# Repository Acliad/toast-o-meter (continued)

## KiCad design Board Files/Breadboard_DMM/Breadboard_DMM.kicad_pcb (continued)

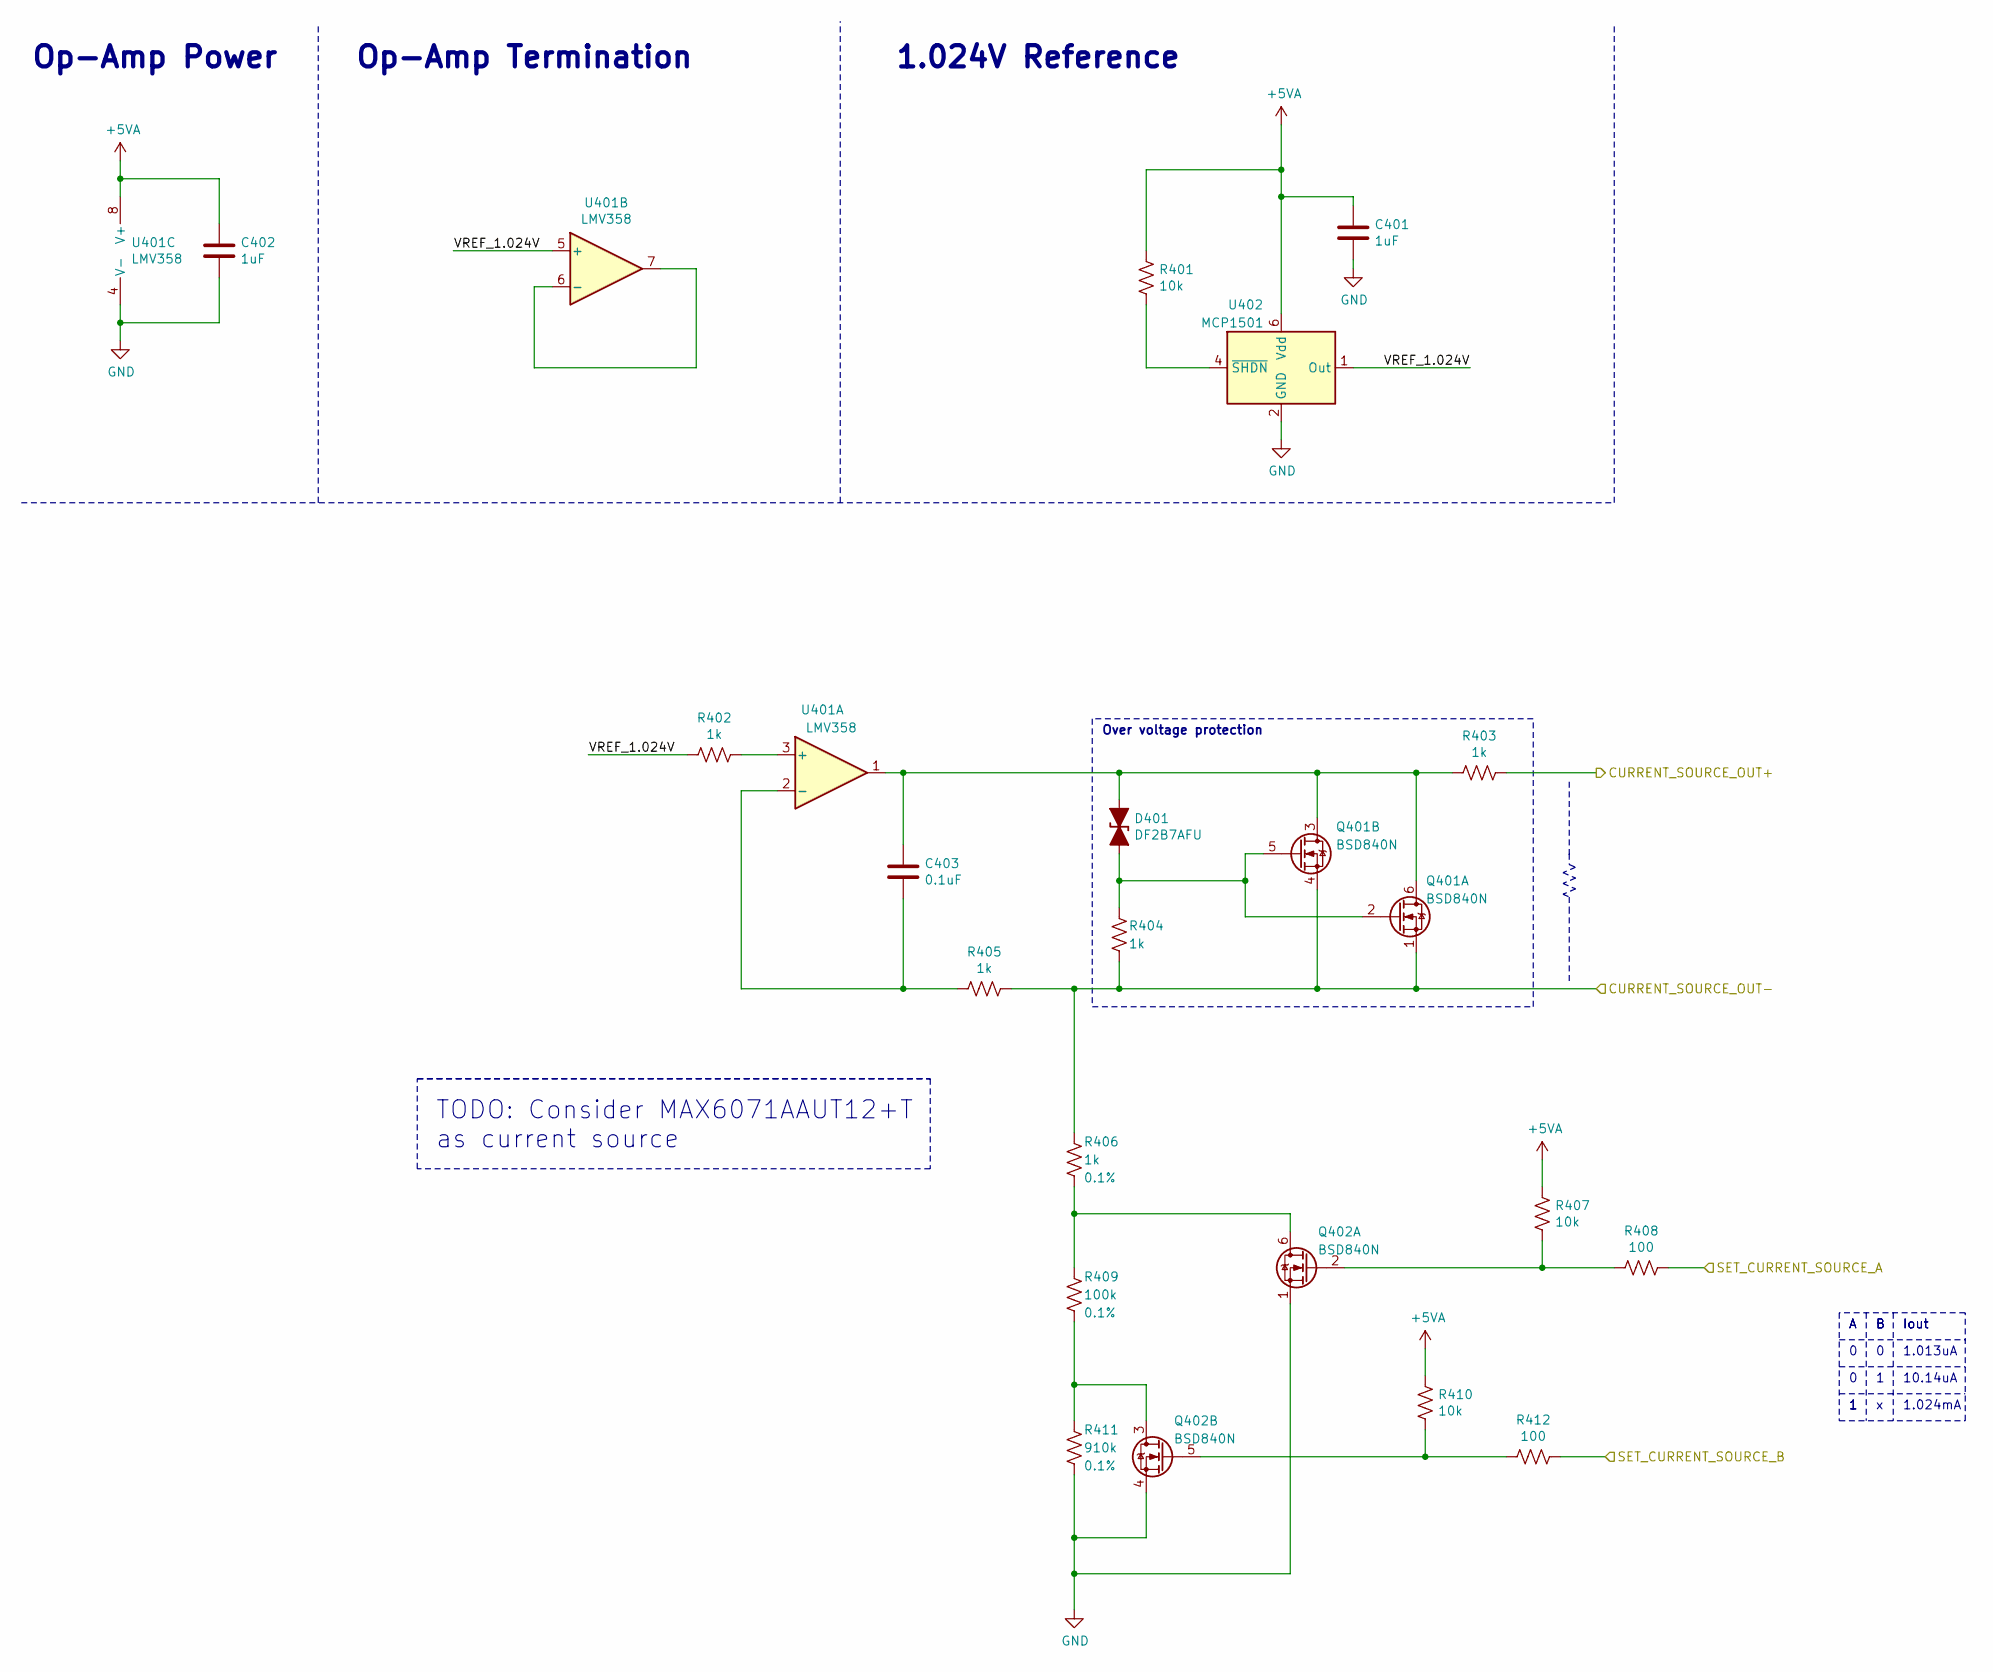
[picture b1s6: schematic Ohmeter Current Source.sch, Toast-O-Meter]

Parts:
C401, C402: 1uF; C_0603_1608Metric_Pad1.08x0.95mm_HandSolder; Digi-Key PN 1276-6524-1-ND
C403: 0.1uF; C_0603_1608Metric_Pad1.08x0.95mm_HandSolder; Digi-Key PN 1276-1006-1-ND
D401: DF2B7AFU; D_SOD-323_HandSoldering; MPN DF2B7AFU; Digi-Key PN DF2B7AFUH3FCT-ND
Q401, Q402: BSD840N; SOT-363_SC-70-6_Handsoldering; MPN BSD840NH6327XTSA1; Digi-Key PN BSD840NH6327XTSA1CT-ND
R401, R407, R410: 10k; R_0603_1608Metric_Pad1.05x0.95mm_HandSolder; Digi-Key PN 311-10.0KHRCT-ND
R402, R403, R404, R405: 1k; R_0603_1608Metric_Pad1.05x0.95mm_HandSolder; Digi-Key PN 311-1.00KHRCT-ND
R406: 1k; R_0805_2012Metric_Pad1.15x1.40mm_HandSolder; Tolerance 0.1%; Digi-Key PN YAG1820CT-ND
R408, R412: 100; R_0603_1608Metric_Pad1.05x0.95mm_HandSolder; Digi-Key PN 311-100HRCT-ND
R409: 100k; R_0805_2012Metric_Pad1.15x1.40mm_HandSolder; Tolerance 0.1%; Digi-Key PN YAG1759CT-ND
R411: 910k; R_0805_2012Metric_Pad1.15x1.40mm_HandSolder; Tolerance 0.1%; Digi-Key PN YAG1993CT-ND
U401: LMV358; SOIC-8_3.9x4.9mm_P1.27mm; Digi-Key PN 296-47593-1-ND
U402: MCP1501; SOT-23-6; Digi-Key PN MCP1501T-10E/CHYCT-ND

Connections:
+5VA: C401.1, C402.1, R401.1, R407.1, R410.1, U401.8 (V+), U402.6 (Vdd); also elsewhere on the board
/Front End/CURRENT_SOURCE_-: Q401.1 (S1), Q401.4 (S2), R404.1, R405.1, R406.1; also elsewhere on the board
/Front End/Ohmeter Current Source/CURRENT_SOURCE_OUT+: R403.1; also elsewhere on the board
/Front End/Ohmeter Current Source/VREF_1.024V: R402.2, U401.5 (+), U402.1 (Out)
/Front End/SET_CURRENT_SOURCE_A: R408.2; also elsewhere on the board
/Front End/SET_CURRENT_SOURCE_B: R412.2; also elsewhere on the board
GND: C401.2, C402.2, Q402.1 (S1), Q402.4 (S2), R411.2, U401.4 (V-), U402.2 (GND), U402.3 (GND), U402.5 (GND); also elsewhere on the board
unnamed: C403.1, D401.1 (A1), Q401.3 (D2), Q401.6 (D1), R403.2, U401.1
unnamed: C403.2, R405.2, U401.2 (-)
unnamed: D401.2 (A2), Q401.2 (G1), Q401.5 (G2), R404.2
unnamed: Q402.2 (G1), R407.2, R408.1
unnamed: Q402.3 (D2), R409.2, R411.1
unnamed: Q402.5 (G2), R410.2, R412.1
unnamed: Q402.6 (D1), R406.2, R409.1
unnamed: R401.2, U402.4 (~SHDN~)
unnamed: R402.1, U401.3 (+)
unnamed: U401.6 (-), U401.7

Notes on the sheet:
Op-Amp Power
1.024V Reference
Op-Amp Termination
Iout
1.013uA
10.14uA
1.024mA
Over voltage protection
TODO: Consider MAX6071AAUT12+T as current source

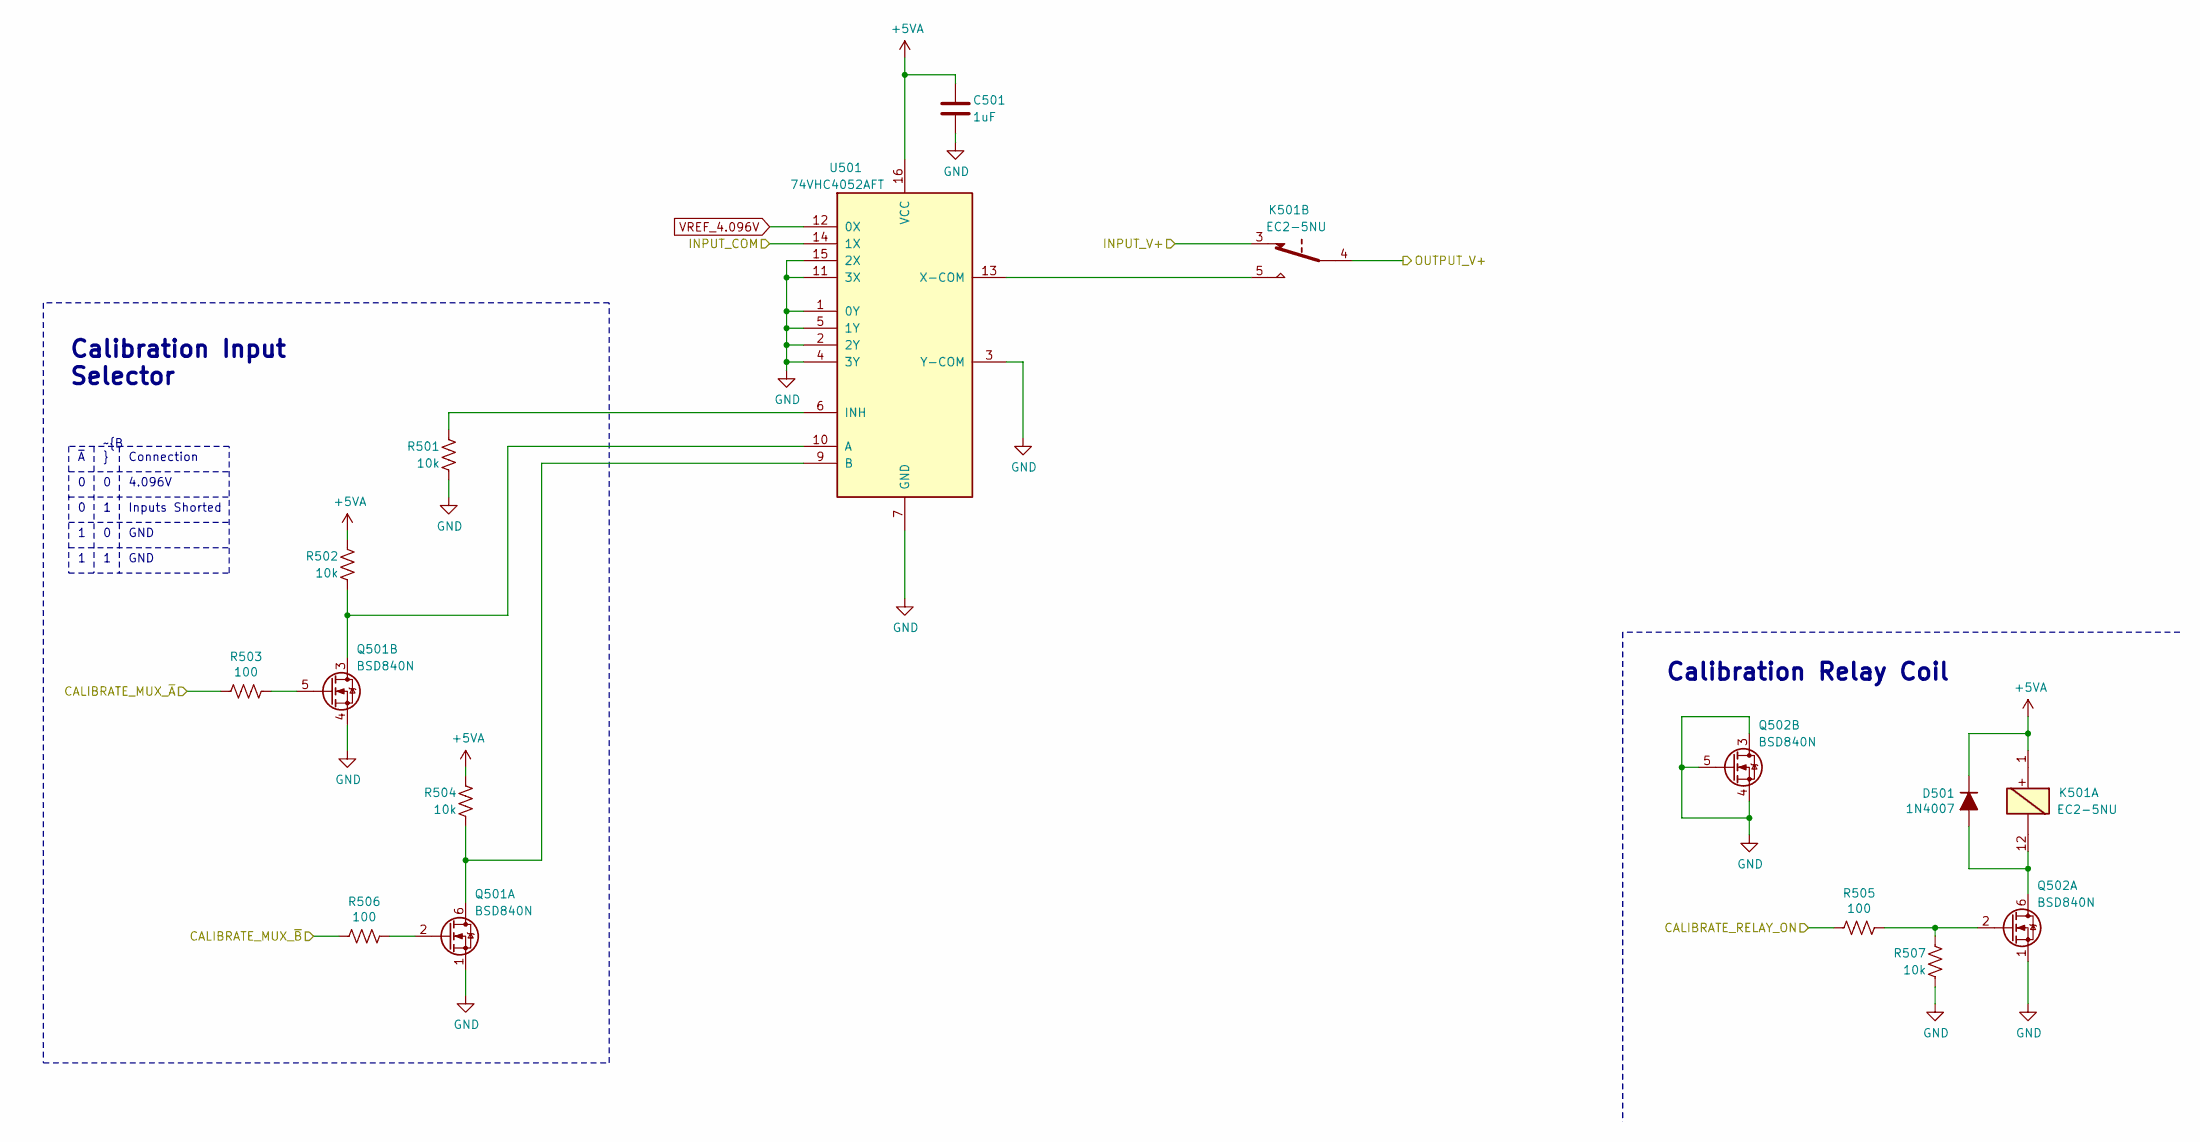
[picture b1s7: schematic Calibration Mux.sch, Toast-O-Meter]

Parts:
C501: 1uF; C_0603_1608Metric_Pad1.08x0.95mm_HandSolder; Digi-Key PN 1276-6524-1-ND
D501: 1N4007; D_SOD-123; Digi-Key PN 1655-1N4007FLCT-ND
K501: EC2-5NU; Relay_DPDT_Kemet_EC2; MPN EC2-5NU; Digi-Key PN 399-11052-5-ND
Q501, Q502: BSD840N; SOT-363_SC-70-6_Handsoldering; MPN BSD840NH6327XTSA1; Digi-Key PN BSD840NH6327XTSA1CT-ND
R501, R502, R504, R507: 10k; R_0603_1608Metric_Pad1.05x0.95mm_HandSolder; Digi-Key PN 311-10.0KHRCT-ND
R503, R505, R506: 100; R_0603_1608Metric_Pad1.05x0.95mm_HandSolder; Digi-Key PN 311-100HRCT-ND
U501: 74VHC4052AFT; TSSOP-16_4.4x5mm_P0.65mm; Digi-Key PN 74VHC4052AFTCT-ND

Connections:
+5VA: C501.1, D501.1 (K), K501.1, R502.1, R504.1, U501.16 (VCC); also elsewhere on the board
/ADC/V-_INPUT: U501.14 (1X); also elsewhere on the board
/Front End/CALIBRATE_MUX_~A: R503.1; also elsewhere on the board
/Front End/CALIBRATE_MUX_~B: R506.1; also elsewhere on the board
/Front End/CALIBRATE_RELAY_ON: R505.1; also elsewhere on the board
/Front End/Calibration Mux/OUTPUT_V+: K501.4; also elsewhere on the board
/Front End/V+: K501.3; also elsewhere on the board
GND: C501.2, Q501.1 (S1), Q501.4 (S2), Q502.1 (S1), Q502.3 (D2), Q502.4 (S2), Q502.5 (G2), R501.2, R507.2, U501.1 (0Y), U501.2 (2Y), U501.3 (Y-COM), U501.4 (3Y), U501.5 (1Y), U501.7 (GND), U501.8 (GND), U501.11 (3X), U501.15 (2X); also elsewhere on the board
unnamed: D501.2 (A), K501.12, Q502.6 (D1)
unnamed: K501.5, U501.13 (X-COM)
unnamed: Q501.2 (G1), R506.2
unnamed: Q501.3 (D2), R502.2, U501.10 (A)
unnamed: Q501.5 (G2), R503.2
unnamed: Q501.6 (D1), R504.2, U501.9 (B)
unnamed: Q502.2 (G1), R505.2, R507.1
unnamed: R501.1, U501.6 (INH)
VREF_4.096V: U501.12 (0X); also elsewhere on the board

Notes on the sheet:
GND
Calibration Relay Coil
Calibration Input Selector
Inputs Shorted
4.096V
Connection

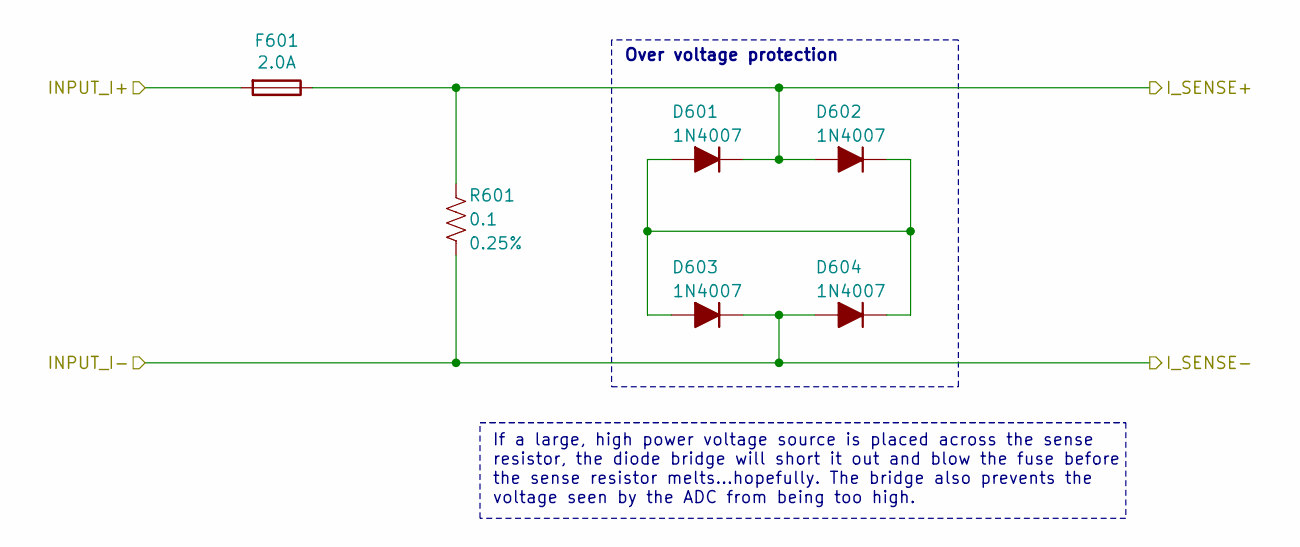
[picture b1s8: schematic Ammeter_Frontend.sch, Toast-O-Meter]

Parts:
D601, D602, D603, D604: 1N4007; D_SOD-123; Digi-Key PN 1655-1N4007FLCT-ND
F601: 2.0A; Fuseholder_Littelfuse_Nano2_154x; Digi-Key PN F1224TR-ND
R601: 0.1; R_Shunt_Ohmite_LVK24; Tolerance 0.25%; Digi-Key PN 273-LVK24R100CERDKR-ND

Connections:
/ADC/I_SENSE+: D601.1 (K), D602.2 (A), F601.1, R601.1; also elsewhere on the board
/ADC/I_SENSE-: D603.1 (K), D604.2 (A), R601.2; also elsewhere on the board
/Front End/I+: F601.2; also elsewhere on the board
unnamed: D601.2 (A), D602.1 (K), D603.2 (A), D604.1 (K)

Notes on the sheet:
Over voltage protection
If a large, high power voltage source is placed across the sense resistor, the diode bridge will short it out and blow the fuse before the sense resistor melts…hopefully. The bridge also prevents the voltage seen by the ADC from being too high.

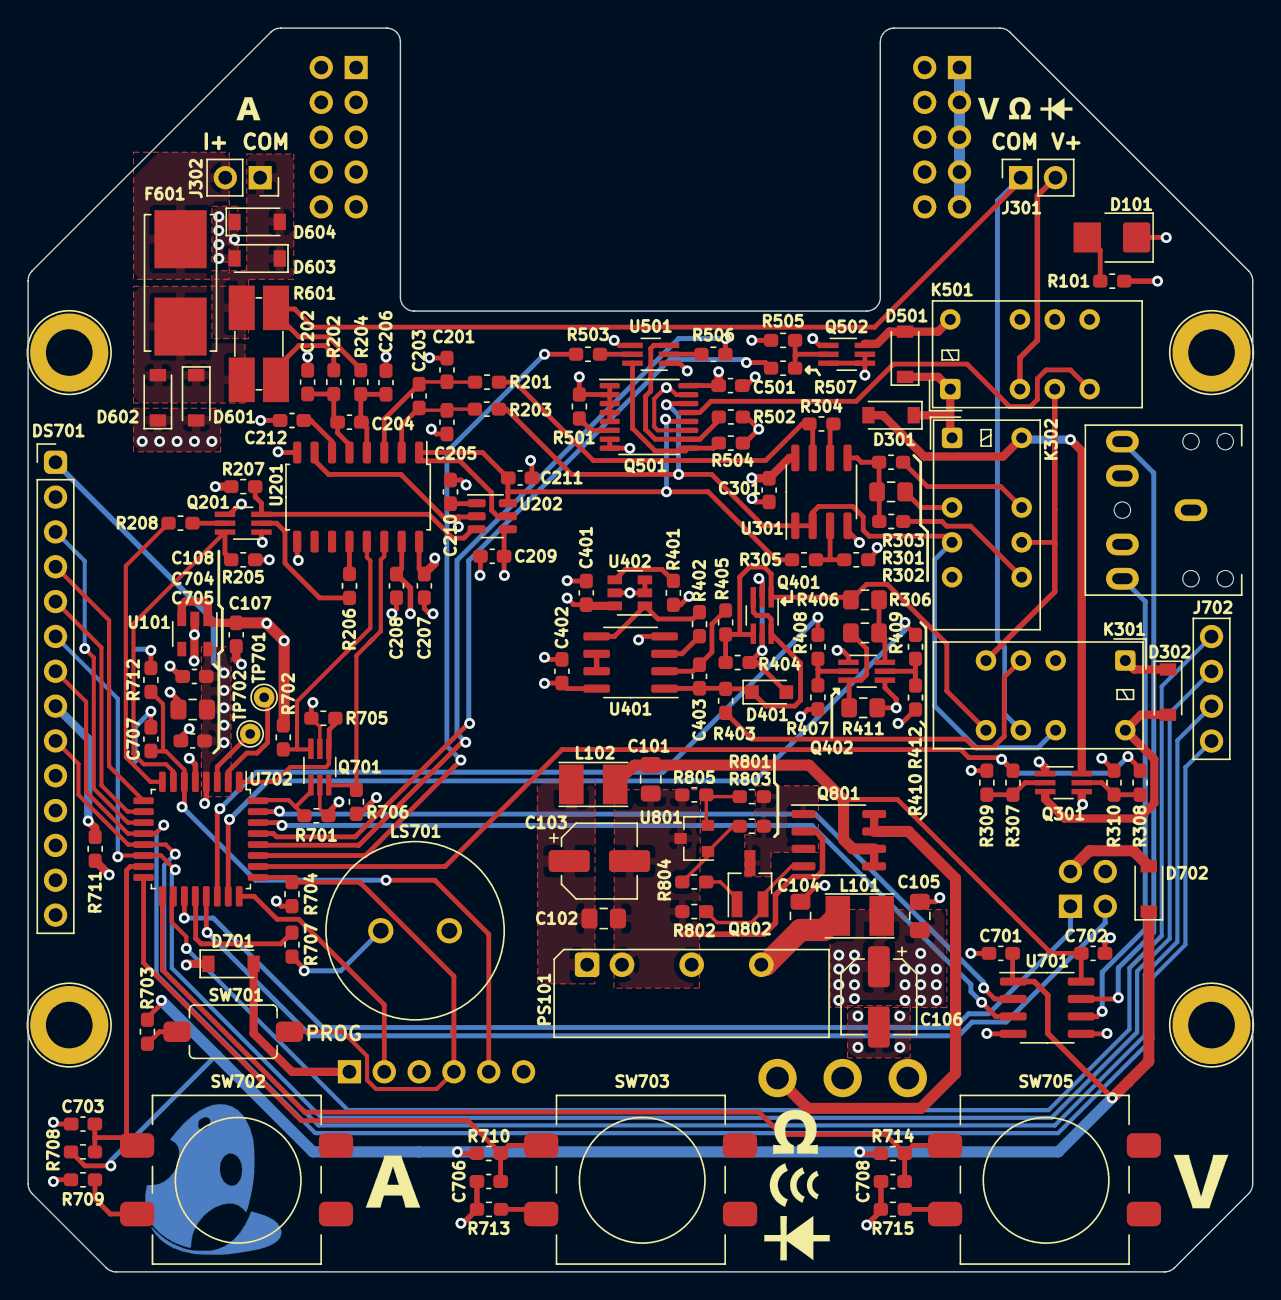
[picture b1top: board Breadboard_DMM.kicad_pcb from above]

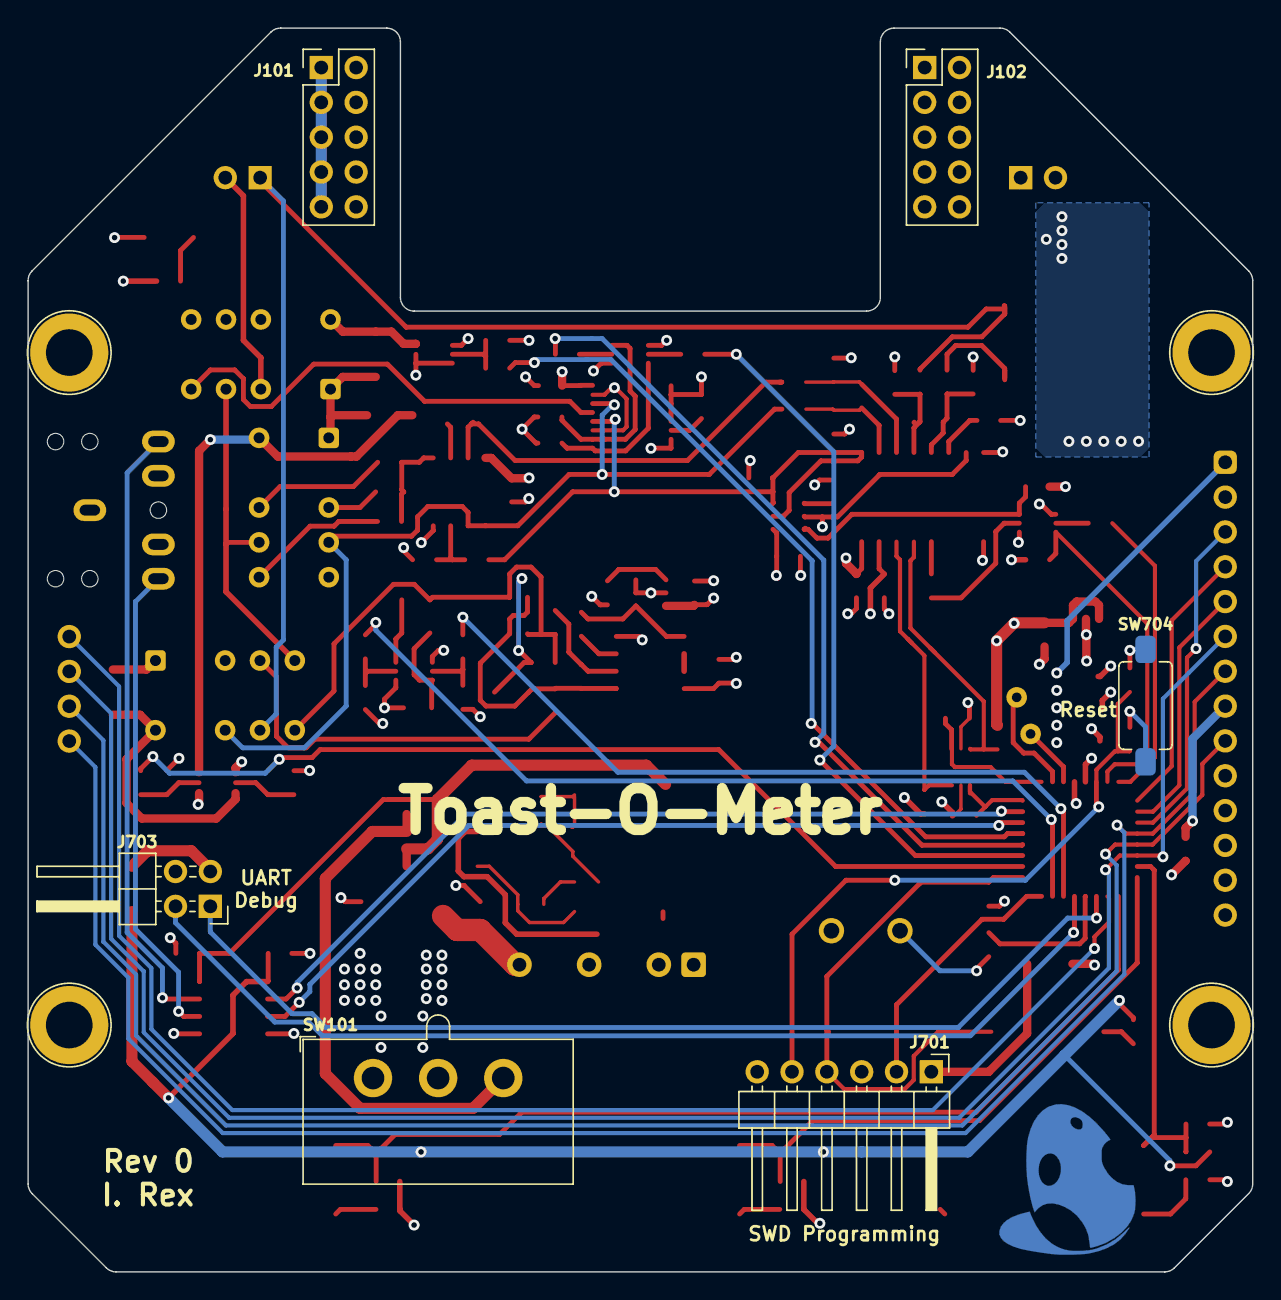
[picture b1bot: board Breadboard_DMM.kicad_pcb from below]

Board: 4 copper layers, 89.3 x 90.7 mm, 146 parts (6 on the bottom side), 108 nets.

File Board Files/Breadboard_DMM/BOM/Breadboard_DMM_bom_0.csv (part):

Component,References,Value,Quantity Per PCB,Footprint,Digi-Key PN,Digi-Key Link,Datasheet
1,C209 C210 C211 C212 C403 C701 C702 C703 C705 C706 C707 C708,0.1uF,12,C_0603_1608Metric_Pad1.08x0.95mm_HandSolder,1276-1006-1-ND,https://www.digikey.com/en/products/detail/samsung-electro-m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,~
2,C107 C108 C201 C202 C203 C204 C205 C206 C207 C208 C301 C401 C402 C501,1uF,14,C_0603_1608Metric_Pad1.08x0.95mm_HandSolder,1276-6524-1-ND,https://www.digikey.com/en/products/detail/samsung-electro-m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,~
3,C101 C102 C104 C105 C704,4.7uF,5,C_0805_2012Metric_Pad1.18x1.45mm_HandSolder,1276-6462-1-ND,https://www.digikey.com/en/products/detail/samsung-electro-m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,~
4,C103 C106,22uF,2,CP_Elec_5x5.3,732-8505-1-ND,https://www.digikey.com/en/products/detail/würth-elektronik/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,~
5,D301 D302 D501 D601 D602 D603 D604 D701 D702,1N4007,9,D_SOD-123,1655-1N4007FLCT-ND,https://www.digikey.com/en/products/detail/smc-diode-solutio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,http://www.smc-diodes.com/propdf/1N4001FL-1N4007FL%20N1646%2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
6,D401,DF2B7AFU,1,D_SOD-323_HandSoldering,DF2B7AFUH3FCT-ND,https://www.digikey.com/en/products/detail/toshiba-semicondu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,https://toshiba.semicon-storage.com/info/docget.jsp?did=5558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
7,D101,Pink,1,LED_Kingbright_AA3528V_3.5x2.8mm_handsolder,754-1534-1-ND,https://www.digikey.com/en/products/detail/kingbright/AA3528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,https://www.kingbrightusa.com/images/catalog/SPEC/AA3528VRVCS-A.pdf
8,DS701,LCD-Generic_3.2in_SPI_SD,1,LCD-Generic-3.2in_89.30x55.04mm_ReducedCourtyard,SAM1093-04-ND; SAM1093-14-ND,https://www.digikey.com/en/products/detail/samtec-inc/SLW-10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 ; https://www.digikey.com/en/products/detail/samtec-inc/SLW-11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,"https://www.aliexpress.com/item/4001122632293.html?spm=a2g0o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,searchweb201602_,searchweb201603_"
9,F601,2.0A,1,Fuseholder_Littelfuse_Nano2_154x,F1224TR-ND,https://www.digikey.com/en/products/detail/littelfuse-inc/01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,https://www.littelfuse.com/~/media/electronics/datasheets/fu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
10,J702,AudioJack3,1,Jack_3.5mm_CUI_SJ1-3523N_Horizontal,CP1-3523N-ND,https://www.digikey.com/en/products/detail/cui-devices/SJ1-3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,~
11,J301 J302,Conn_01x02,2,PinSocket_1x02_P2.54mm_Vertical,SAM1213-02-ND,https://www.digikey.com/en/products/detail/samtec-inc/SSW-10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,~
12,J701,Conn_01x06,1,PinHeader_1x06_P2.54mm_Horizontal,2057-PH1RA-06-UA-ND,https://www.digikey.com/en/products/detail/adam-tech/ph1ra-0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,~
13,J703,Conn_02x02_Top_Bottom,1,PinHeader_2x02_P2.54mm_Horizontal,2057-PH2RA-04-UA-ND,https://www.digikey.com/en/products/detail/adam-tech/PH2RA-0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,~
14,J101 J102,Conn_02x05_Odd_Even,2,PinHeader_2x05_P2.54mm_Vertical,2057-PH2-10-UA-ND,https://www.digikey.com/en/products/detail/adam-tech/PH2-10-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,~
15,K301 K302 K501,EC2-5NU,3,Relay_DPDT_Kemet_EC2,399-11052-5-ND,https://www.digikey.com/en/products/detail/kemet/EC2-5NU/4291118,https://content.kemet.com/datasheets/KEM_R7002_EC2_EE2.pdf
16,L101 L102,6.8uH,2,L_Taiyo-Yuden_NR-30xx_HandSoldering,587-2592-1-ND,https://www.digikey.com/en/products/detail/taiyo-yuden/NRH30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,https://ds.yuden.co.jp/TYCOMPAS/ut/detail?pn=NRH3012T6R8MN%2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
17,LS701,PKM13EPYH4000-A0,1,Buzzer_Murata_PKM13EPYH4000-A0_D12.6mm_H6.9mm,490-4698-1-ND,https://www.digikey.com/en/products/detail/murata-electronic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,https://www.murata.com/~/media/webrenewal/support/library/ca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
18,PS101,PDME1-S5-S5-S,1,CUI_DCDC-CONVERTER_PDME1-Sxx-S_1x4_P2.54mm_Drill1.0mm,102-6320-ND,https://www.digikey.com/en/products/detail/cui-inc/PDME1-S5-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,https://www.cui.com/product/resource/pdme1-s.pdf
19,Q201 Q301 Q401 Q402 Q501 Q502 Q701,BSD840N,7,SOT-363_SC-70-6_Handsoldering,BSD840NH6327XTSA1CT-ND,https://www.digikey.com/en/products/detail/infineon-technolo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,https://www.infineon.com/dgdl/BSD840N_Rev2.3_.pdf?folderId=d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
20,Q801,DMP3085LSD,1,SO-8_3.9x4.9mm_P1.27mm,DMP3085LSD-13DICT-ND,https://www.digikey.com/en/products/detail/diodes-incorporat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,https://www.diodes.com/assets/Datasheets/DMP3085LSD.pdf
21,Q802,PMBT2907A,1,SOT-23_Handsoldering,1727-2958-1-ND,https://www.digikey.com/en/products/detail/nexperia-usa-inc/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,https://media.digikey.com/pdf/Data%20Sheets/NXP%20PDFs/PMBT2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
22,R601,0.1,1,R_Shunt_Ohmite_LVK24,273-LVK24R100CERDKR-ND,https://www.digikey.com/en/products/detail/ohmite/LVK24R100C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,~
23,R201 R202 R203 R204 R206 R208 R307 R308 R408 R412 R503 R505 R506 R711,100,14,R_0603_1608Metric_Pad1.05x0.95mm_HandSolder,311-100HRCT-ND,https://www.digikey.com/en/products/detail/yageo/RC0603FR-07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,~
24,R101 R402 R403 R404 R405 R707 R709 R712 R713 R715,1k,10,R_0603_1608Metric_Pad1.05x0.95mm_HandSolder,311-1.00KHRCT-ND,https://www.digikey.com/en/products/detail/yageo/RC0603FR-07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,~
25,R406,1k,1,R_0805_2012Metric_Pad1.15x1.40mm_HandSolder,YAG1820CT-ND,https://www.digikey.com/en/products/detail/yageo/RT0805BRD07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,~
26,R801,1.5k,1,R_0603_1608Metric_Pad1.05x0.95mm_HandSolder,311-1.50KHRCT-ND,https://www.digikey.com/en/products/detail/yageo/RC0603FR-07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,~
27,R701 R702 R705 R706,4.7k,4,R_0603_1608Metric_Pad1.05x0.95mm_HandSolder,311-4.70KHRCT-ND,https://www.digikey.com/en/products/detail/yageo/RC0603FR-07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,~
28,R205 R207 R305 R306 R309 R310 R401 R407 R410 R501 R502 R504 R507 R708 R710 R714 R802 R804 R805,10k,19,R_0603_1608Metric_Pad1.05x0.95mm_HandSolder,311-10.0KHRCT-ND,https://www.digikey.com/en/products/detail/yageo/RC0603FR-07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,~
29,R703 R704,10k,2 (DNF),R_0603_1608Metric_Pad1.05x0.95mm_HandSolder,311-10.0KHRCT-ND,https://www.digikey.com/en/products/detail/yageo/RC0603FR-07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,~
30,R803,12k,1,R_0603_1608Metric_Pad1.05x0.95mm_HandSolder,311-12.0KHRCT-ND,https://www.digikey.com/en/products/detail/yageo/RC0603FR-07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,~
31,R409,100k,1,R_0805_2012Metric_Pad1.15x1.40mm_HandSolder,YAG1759CT-ND,https://www.digikey.com/en/products/detail/yageo/RT0805BRD07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,~
32,R302 R304,750k,2,R_0603_1608Metric_Pad1.05x0.95mm_HandSolder,311-750KHRCT-ND,https://www.digikey.com/en/products/detail/yageo/RC0603FR-07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,~
33,R303,820k,1,R_0805_2012Metric_Pad1.15x1.40mm_HandSolder,RR12P820KDCT-ND,https://www.digikey.com/en/products/detail/susumu/RR1220P-82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,~
34,R411,910k,1,R_0805_2012Metric_Pad1.15x1.40mm_HandSolder,YAG1993CT-ND,https://www.digikey.com/en/products/detail/yageo/RT0805BRD07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,~
35,R301,10M,1,R_0603_1608Metric_Pad1.05x0.95mm_HandSolder,541-10MAYCT-ND,https://www.digikey.com/en/products/detail/vishay-dale/CRCW0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,~
36,SW101,L102021ML04Q,1,SW_CuK_L102021ML04Q_SPDT_Angled,CKC5102-ND,https://www.digikey.com/en/products/detail/c-k/L102021ML04Q/181454,https://www.ckswitches.com/media/1423/l.pdf
37,SW701 SW704,SW_Push,2 (DNF),SW-PUSH-6x3.5mm_CK-PTS636SL43x_HandSolder,CKN12309-1-ND,https://www.digikey.com/en/products/detail/c-k/PTS636-SL43-S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,~
38,SW702 SW703 SW705,SW_Push,3,SW_PUSH-12mm_Wuerth-430476085716_HandSolder,732-13655-1-ND,https://www.digikey.com/en/products/detail/würth-elektronik/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,~
39,U501,74VHC4052AFT,1,TSSOP-16_4.4x5mm_P0.65mm,74VHC4052AFTCT-ND,https://www.digikey.com/en/products/detail/toshiba-semicondu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,https://www.mouser.com/datasheet/2/408/74VHC4052AFT_datashee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
40,U301 U401,LMV358,2,SOIC-8_3.9x4.9mm_P1.27mm,296-47593-1-ND,https://www.digikey.com/en/products/detail/texas-instruments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,http://www.ti.com/lit/ds/symlink/lmv324.pdf
41,U202,MAX6070x41,1,SOT-23-6,MAX6070AAUT41+TCT-ND,https://www.digikey.com/en/products/detail/maxim-integrated/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,https://datasheets.maximintegrated.com/en/ds/MAX6070-MAX6071.pdf
42,U402,MCP1501,1,SOT-23-6,MCP1501T-10E/CHYCT-ND,https://www.digikey.com/en/products/detail/microchip-technol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,http://ww1.microchip.com/downloads/en/DeviceDoc/20005474E.pdf
43,U101,MIC5365-3.3YD5,1,SOT-23-5,576-4085-1-ND,https://www.digikey.com/en/products/detail/microchip-technol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,http://ww1.microchip.com/downloads/en/DeviceDoc/mic5365.pdf
44,U201,NAU7802,1,SOP-16_4.55x10.3mm_P1.27mm,NAU7802SGI-ND,https://www.digikey.com/en/products/detail/nuvoton-technolog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,https://www.nuvoton.com/export/resource-files/NAU7802%20Data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
45,U701,SI8422,1,SOIC-8_3.9x4.9mm_P1.27mm,SI8422AB-D-IS-ND,https://www.digikey.com/en/products/detail/silicon-labs/SI84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,https://www.silabs.com/documents/public/data-sheets/si841x-2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

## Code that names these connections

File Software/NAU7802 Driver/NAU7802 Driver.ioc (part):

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Mcu.Name=STM32G071R(6-8-B)Tx
Mcu.Package=LQFP64
Mcu.UserName=STM32G071RBTx
PA13.GPIOParameters=GPIO_Label
PA13.GPIO_Label=TMS
PA13.Mode=Serial_Wire
PA13.Signal=SYS_SWDIO
PA14-BOOT0.GPIOParameters=GPIO_Label
PA14-BOOT0.GPIO_Label=TCK
PA14-BOOT0.Mode=Serial_Wire
PA14-BOOT0.Signal=SYS_SWCLK
PA2.GPIOParameters=GPIO_PuPd,GPIO_Label
PA2.GPIO_Label=USART2_TX [STLK_TX]
PA2.GPIO_PuPd=GPIO_PULLUP
PA2.Mode=Asynchronous
PA2.Signal=USART2_TX
PA3.GPIOParameters=GPIO_PuPd,GPIO_Label
PA3.GPIO_Label=USART2_RX [STLK_RX]
PA3.GPIO_PuPd=GPIO_PULLUP
PA3.Mode=Asynchronous
PA3.Signal=USART2_RX
PA5.GPIOParameters=GPIO_Speed,GPIO_Label
PA5.GPIO_Label=LED_GREEN
PA5.GPIO_Speed=GPIO_SPEED_FREQ_HIGH
PA5.Signal=GPIO_Output
PB8.Mode=I2C
PB8.Signal=I2C1_SCL
PB9.Mode=I2C
PB9.Signal=I2C1_SDA
PC13.Mode=SYS_WakeUp1
PC13.Signal=SYS_WKUP2
PC14-OSC32_IN\ (PC14).Mode=LSE-External-Oscillator
PC14-OSC32_IN\ (PC14).Signal=RCC_OSC32_IN
PC15-OSC32_OUT\ (PC15).Mode=LSE-External-Oscillator
PC15-OSC32_OUT\ (PC15).Signal=RCC_OSC32_OUT
PF0-OSC_IN\ (PF0).GPIOParameters=GPIO_Label
PF0-OSC_IN\ (PF0).GPIO_Label=MCO
PF0-OSC_IN\ (PF0).Mode=HSE-External-Clock-Source
PF0-OSC_IN\ (PF0).Signal=RCC_OSC_IN
RCC.HSE_VALUE=8000000
RCC.SYSCLKFreq_VALUE=16000000
board=NUCLEO-G071RB
boardIOC=true

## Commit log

2020-08-20 Cleaned up system files
2020-08-21 Started cleaning up front end page
2020-08-27 Starting converting to hierachichal design
2020-08-30 Added new sheet for main supply measurement, added upgrades document
2020-09-26 Finished main design, cleaning up schematic
2020-10-02 Finished main cleanup, started adding digikey part numbers
2020-10-03 Started adding Digikey links
2020-10-06 Finished adding parts, cleaned up, ran ERC
2020-10-06 Cleaned up files
2020-10-21 Updated probe connector arrangement
2020-11-14 Semi-finished component placement
2020-11-15 59 unrouted nodes
2020-11-21 Added silkscreen graphics and BOM
2021-01-10 Updated Digikey link for power isolator, started ADC driver
2021-01-11 Outlined function prototypes
2021-01-11 Wrote about 1/3 of functions
2021-01-16 Finished ADC driver writing functions, almost done with read functions
2021-01-17 Finished untested .c file
2021-01-17 Fixed some compiler warnings
2021-01-17 Fixed .gitignore files
2021-01-17 Updated gitignore, began basic testing
2021-01-19 Updated U801 DK link and part number, updated change log
2021-02-17 Updated changelog
